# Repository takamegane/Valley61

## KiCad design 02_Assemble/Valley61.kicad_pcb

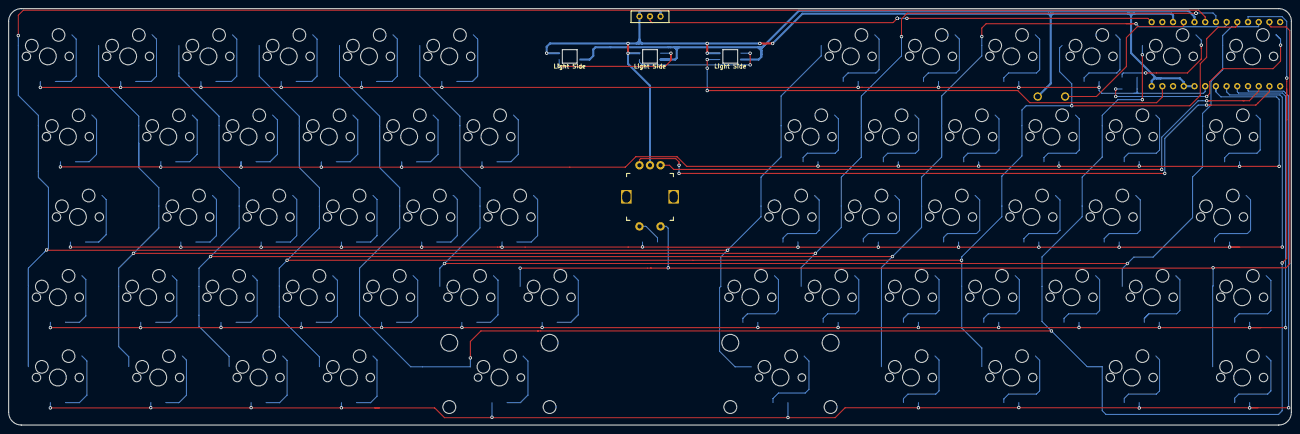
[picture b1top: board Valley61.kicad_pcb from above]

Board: 2 copper layers, 304.4 x 98.8 mm, 128 parts (0 on the bottom side), 82 nets.

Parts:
D1, D2, D3, D4, D5, D6, D7, D8, D9, D10, D11, D12, D13, D14, D15, D16, D17, D18, D19, D20, D21, D22, D23, D24, D25, D26, D27, D28, D29, D30, D31, D32, D33, D34, D35, D36, D37, D38, D39, D40, D41, D42, D43, D44, D45, D46, D47, D48, D49, D50, D51, D52, D53, D54, D55, D56, D57, D58, D59, D60, D61: D; Diode_SMD
J1: Conn_01x02; Battery_XH2.5_GL_PCB
L1, L2, L3: SK6812MINI; LED_SK6812MINI-E_BL
SW1, SW6, SW7, SW8, SW9, SW11, SW12, SW13, SW14, SW16, SW17, SW18, SW19, SW20, SW21, SW22, SW23, SW24, SW26, SW27, SW28, SW29, SW31, SW32, SW33, SW34, SW35, SW37, SW38, SW39, SW40, SW41, SW42, SW43, SW44, SW45, SW46, SW47, SW48, SW49, SW52, SW53, SW54, SW59: SW_PUSH; CherryMX_Hotswap_1.0u
SW2, SW50, SW55, SW57: SW_PUSH; CherryMX_Hotswap_1.5u
SW3, SW58: SW_PUSH; CherryMX_Hotswap_1.75u
SW4, SW5, SW10, SW15, SW60, SW61: SW_PUSH; CherryMX_Hotswap_1.25u
SW25: SW_PUSH; CherryMX_Hotswap_2.75u_Rev
SW30: Rotary_Encoder_Switch; RotaryEncoder_EC12E
SW36: SW_PUSH; CherryMX_Hotswap_2.25u_Rev
SW51, SW56: SW_PUSH; CherryMX_Hotswap_1.0u_Small1
SW62: SW_PUSH; ResetSW
U1: BLEMicroPro; Micon_BMP_GL

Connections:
A1: SW30.A, U1.10
B1: SW30.B, U1.11
Bat+: J1.1, U1.25
Col0: SW1.1, SW2.1, SW3.1, SW4.1, SW5.1, SW32.1, SW33.1, SW34.1, SW35.1, SW36.1, U1.20
Col1: SW6.1, SW7.1, SW8.1, SW9.1, SW10.1, SW37.1, SW38.1, SW39.1, SW40.1, U1.19
Col2: SW11.1, SW12.1, SW13.1, SW14.1, SW15.1, SW41.1, SW42.1, SW43.1, SW44.1, SW45.1, U1.18
Col3: SW16.1, SW17.1, SW18.1, SW19.1, SW20.1, SW46.1, SW47.1, SW48.1, SW49.1, SW50.1, U1.17
Col4: SW21.1, SW22.1, SW23.1, SW24.1, SW25.1, SW51.1, SW52.1, SW53.1, SW54.1, SW55.1, U1.16
Col5: SW26.1, SW27.1, SW28.1, SW29.1, SW56.1, SW57.1, SW58.1, SW59.1, U1.15
Col6: SW30.S2, SW31.1, SW60.1, SW61.1, U1.14
GND: J1.2, L1.2, L2.2, L3.2, SW30.C, SW62.2, U1.3, U1.4, U1.23, U1.26
LED: L1.3, U1.1
unnamed: D1.2, SW1.2
unnamed: D2.2, SW2.2
unnamed: D3.2, SW3.2
unnamed: D4.2, SW4.2
unnamed: D5.2, SW5.2
unnamed: D6.2, SW6.2
unnamed: D7.2, SW7.2
unnamed: D8.2, SW8.2
unnamed: D9.2, SW9.2
unnamed: D10.2, SW10.2
unnamed: D11.2, SW11.2
unnamed: D12.2, SW12.2
unnamed: D13.2, SW13.2
unnamed: D14.2, SW14.2
unnamed: D15.2, SW15.2
unnamed: D16.2, SW16.2
unnamed: D17.2, SW17.2
unnamed: D18.2, SW18.2
unnamed: D19.2, SW19.2
unnamed: D20.2, SW20.2
unnamed: D21.2, SW21.2
unnamed: D22.2, SW22.2
unnamed: D23.2, SW23.2
unnamed: D24.2, SW24.2
unnamed: D25.2, SW25.2
unnamed: D26.2, SW26.2
unnamed: D27.2, SW27.2
unnamed: D28.2, SW28.2
unnamed: D29.2, SW29.2
unnamed: D30.2, SW30.S1
unnamed: D31.2, SW31.2
unnamed: D32.1, SW32.2
unnamed: D33.1, SW33.2
unnamed: D34.1, SW34.2
unnamed: D35.1, SW35.2
unnamed: D36.1, SW36.2
unnamed: D37.1, SW37.2
unnamed: D38.1, SW38.2
unnamed: D39.1, SW39.2
unnamed: D40.1, SW40.2
unnamed: D41.1, SW41.2
unnamed: D42.1, SW42.2
unnamed: D43.1, SW43.2
unnamed: D44.1, SW44.2
unnamed: D45.1, SW45.2
unnamed: D46.1, SW46.2
unnamed: D47.1, SW47.2
unnamed: D48.1, SW48.2
unnamed: D49.1, SW49.2
unnamed: D50.1, SW50.2
unnamed: D51.1, SW51.2
unnamed: D52.1, SW52.2
unnamed: D53.1, SW53.2
unnamed: D54.1, SW54.2
unnamed: D55.1, SW55.2
unnamed: D56.1, SW56.2
unnamed: D57.1, SW57.2
unnamed: D58.1, SW58.2
unnamed: D59.1, SW59.2
unnamed: D60.1, SW60.2
unnamed: D61.1, SW61.2
unnamed: L1.1, L2.3
unnamed: L2.1, L3.3
Reset: SW62.1, U1.22
Row0: D1.1, D6.1, D11.1, D16.1, D21.1, D26.1, D32.2, D37.2, D41.2, D46.2, D51.2, D56.2, U1.5
Row1: D2.1, D7.1, D12.1, D17.1, D22.1, D27.1, D33.2, D38.2, D42.2, D47.2, D52.2, D57.2, U1.6
Row2: D3.1, D8.1, D13.1, D18.1, D23.1, D28.1, D30.1, D34.2, D39.2, D43.2, D48.2, D53.2, D58.2, U1.7
Row3: D4.1, D9.1, D14.1, D19.1, D24.1, D29.1, D31.1, D35.2, D40.2, D44.2, D49.2, D54.2, D59.2, D60.2, U1.8
Row4: D5.1, D10.1, D15.1, D20.1, D25.1, D36.2, D45.2, D50.2, D55.2, D61.2, U1.9
VCC: L1.4, L2.4, L3.4, U1.21

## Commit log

2022-01-08 upload
